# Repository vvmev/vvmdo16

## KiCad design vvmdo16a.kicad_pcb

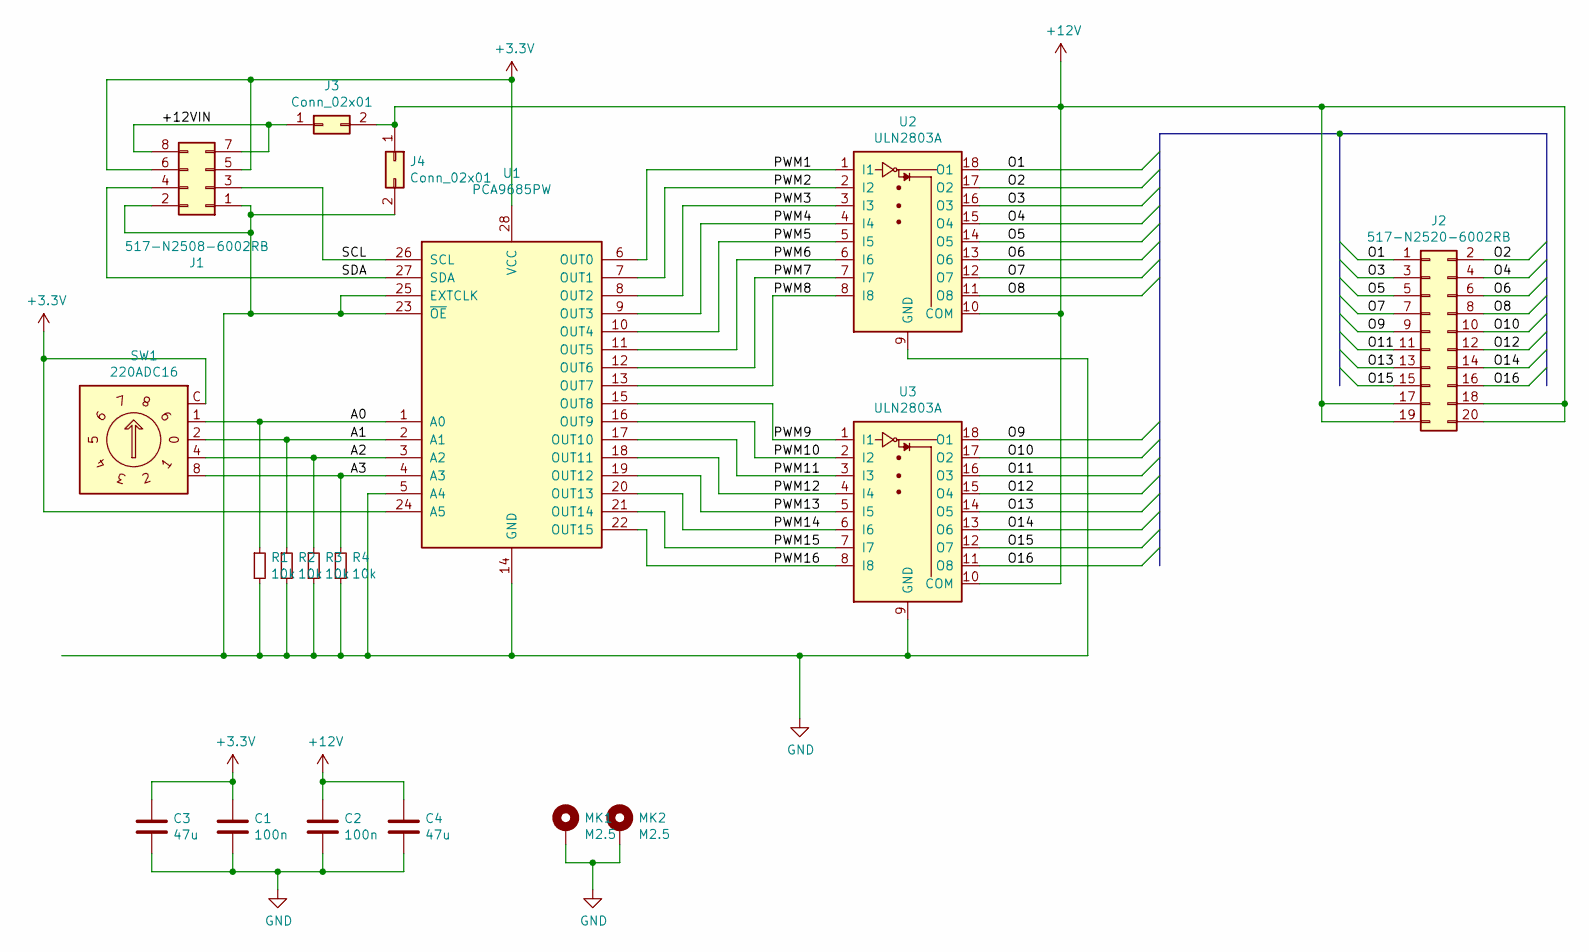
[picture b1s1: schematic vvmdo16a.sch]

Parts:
C1, C2: 100n; C_0805_HandSoldering
C3, C4: 47u; C_0805_HandSoldering
J1: 517-N2508-6002RB; IDC-Header_2x04_P2.54mm_Vertical
J2: 517-N2520-6002RB; IDC-Header_2x10_Pitch2.54mm_Straight
J3: Conn_02x01; Pin_Header_Straight_2x01_Pitch2.54mm
J4: Conn_02x01; TerminalBlock_Phoenix_PT-3.5mm_2pol
MK1, MK2: M2.5; MountingHole_2.7mm_M2.5_DIN965_Pad
R1, R2, R3, R4: 10k; R_0805_HandSoldering
SW1: 220ADC16; Nidec_Copal_SH-7010C
U1: PCA9685PW; TSSOP-28_4.4x9.7mm_Pitch0.65mm
U2, U3: ULN2803A; SOIC-18W_7.5x11.6mm_Pitch1.27mm

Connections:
+3V3: C1.1, C3.1, J1.5, J1.6, SW1.C, U1.24 (A5), U1.28 (VCC)
+12V: C2.1, C4.1, J2.17, J2.18, J2.19, J2.20, J3.2, J4.1, U2.10 (COM), U3.10 (COM)
/+12VIN: J1.7, J1.8, J3.1
/A0: R1.1, SW1.1, U1.1 (A0)
/A1: R2.1, SW1.2, U1.2 (A1)
/A2: R3.1, SW1.4, U1.3 (A2)
/A3: R4.1, SW1.8, U1.4 (A3)
/O1: J2.1, U2.18 (O1)
/O2: J2.2, U2.17 (O2)
/O3: J2.3, U2.16 (O3)
/O4: J2.4, U2.15 (O4)
/O5: J2.5, U2.14 (O5)
/O6: J2.6, U2.13 (O6)
/O7: J2.7, U2.12 (O7)
/O8: J2.8, U2.11 (O8)
/O9: J2.9, U3.18 (O1)
/O10: J2.10, U3.17 (O2)
/O11: J2.11, U3.16 (O3)
/O12: J2.12, U3.15 (O4)
/O13: J2.13, U3.14 (O5)
/O14: J2.14, U3.13 (O6)
/O15: J2.15, U3.12 (O7)
/O16: J2.16, U3.11 (O8)
/PWM1: U1.6 (OUT0), U2.1 (I1)
/PWM2: U1.7 (OUT1), U2.2 (I2)
/PWM3: U1.8 (OUT2), U2.3 (I3)
/PWM4: U1.9 (OUT3), U2.4 (I4)
/PWM5: U1.10 (OUT4), U2.5 (I5)
/PWM6: U1.11 (OUT5), U2.6 (I6)
/PWM7: U1.12 (OUT6), U2.7 (I7)
/PWM8: U1.13 (OUT7), U2.8 (I8)
/PWM9: U1.15 (OUT8), U3.1 (I1)
/PWM10: U1.16 (OUT9), U3.2 (I2)
/PWM11: U1.17 (OUT10), U3.3 (I3)
/PWM12: U1.18 (OUT11), U3.4 (I4)
/PWM13: U1.19 (OUT12), U3.5 (I5)
/PWM14: U1.20 (OUT13), U3.6 (I6)
/PWM15: U1.21 (OUT14), U3.7 (I7)
/PWM16: U1.22 (OUT15), U3.8 (I8)
/SCL: J1.3, U1.26 (SCL)
/SDA: J1.4, U1.27 (SDA)
GND: C1.2, C2.2, C3.2, C4.2, J1.1, J1.2, J4.2, MK1.1, MK2.1, R1.2, R2.2, R3.2, R4.2, U1.5 (A4), U1.14 (GND), U1.23 (~OE~), U1.25 (EXTCLK), U2.9 (GND), U3.9 (GND)

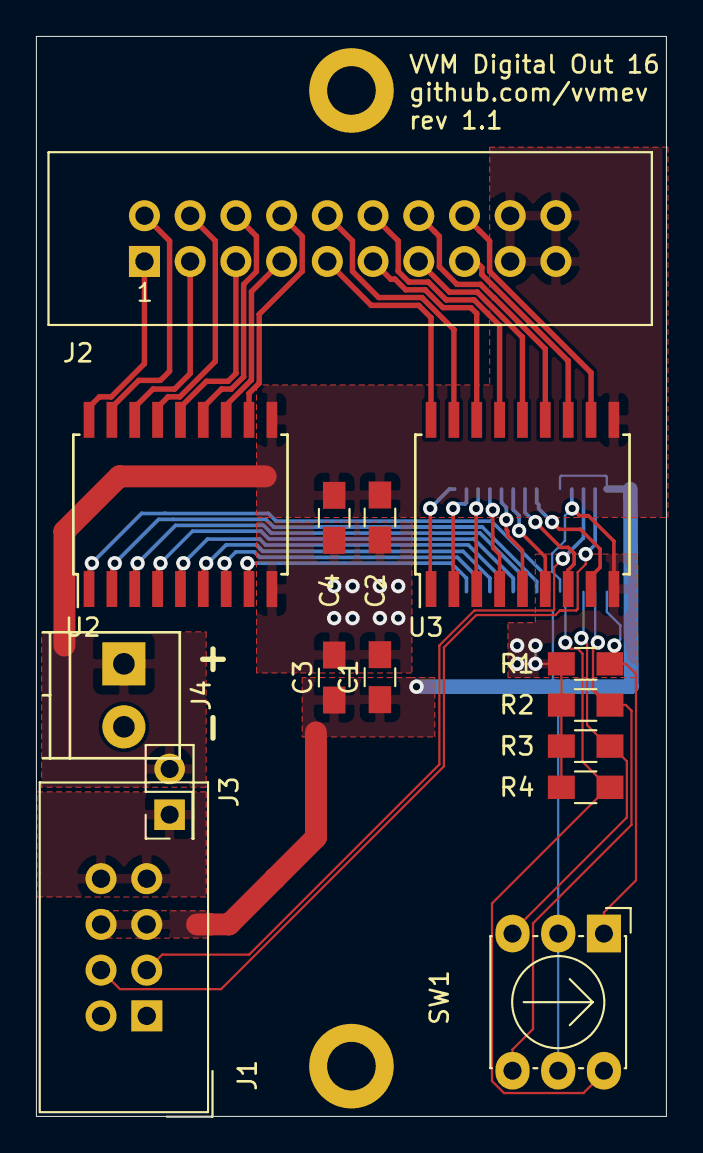
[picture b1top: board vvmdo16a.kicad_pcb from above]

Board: 2 copper layers, 35.0 x 60.0 mm, 18 parts (1 on the bottom side), 42 nets.

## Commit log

2019-05-01 First version
    All components placed and connected, but somewhat too big a PCB.
2019-05-01 remove backup files
2019-05-01 More compact PCB
2019-05-02 Add seperate power rail input Label the board
2019-05-02 correct board name
2019-05-02 Add labels to screw terminal; print schematics
2019-05-05 ready for plotting
2019-05-30 Tie A4 to GND instead of +3V3
    This selects addresses 0x60-0x6f for the IO controller.
    Fixes #1
